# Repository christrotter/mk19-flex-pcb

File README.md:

# mk19-flex-pcb
All credit to: [Cyboard](https://github.com/Cyboard-DigitalTailor/cyboard-public)

Custom flex pcb/cable/thing for the mk19 pcb rev2, an extended version of the Cyboard factory cable.

# ordering notes
## creating gerbers.zip
Follow their docs: 
- https://jlcpcb.com/help/article/495-easyeda-flex-pcb-design-user-guide
- https://jlcpcb.com/help/article/362-how-to-generate-gerber-and-drill-files-in-kicad-7

Ensure you include the User_Drawings layer.

**Example gerber file contents:**
```
mk19-flex-pcb-B_Cu.gbl
mk19-flex-pcb-B_Mask.gbs
mk19-flex-pcb-B_Paste.gbp
mk19-flex-pcb-B_Silkscreen.gbo
mk19-flex-pcb-Edge_Cuts.gm1
mk19-flex-pcb-F_Cu.gtl
mk19-flex-pcb-F_Mask.gts
mk19-flex-pcb-F_Paste.gtp
mk19-flex-pcb-F_Silkscreen.gto
mk19-flex-pcb-NPTH-drl_map.gbr
mk19-flex-pcb-NPTH.drl
mk19-flex-pcb-PTH-drl_map.gbr
mk19-flex-pcb-PTH.drl
mk19-flex-pcb-User_Drawings.gbr
mk19-flex-pcb-gerbers.zip
mk19-flex-pcb-job.gbrjob
```

## submitting the order
- whatever quantity you want
- 0.12 pcb thickness
- polyimide stiffener; 0.1mm
- 0.2mm gold fingers
- colour: white

1. On the initial order page.  The very first page where you add the gerbers.zip file.
2. Veerrrrrrry bottom: 'add pcb remark'
3. Ensure you add a comment in here that says: 
```
Please see 'mk19-flex-pcb-User_Drawings.gbr' for stiffener locations and remarks - there should be only a small amount of stiffener required. I understand this requires extra charges for the small slots - that's fine.
```

# overview

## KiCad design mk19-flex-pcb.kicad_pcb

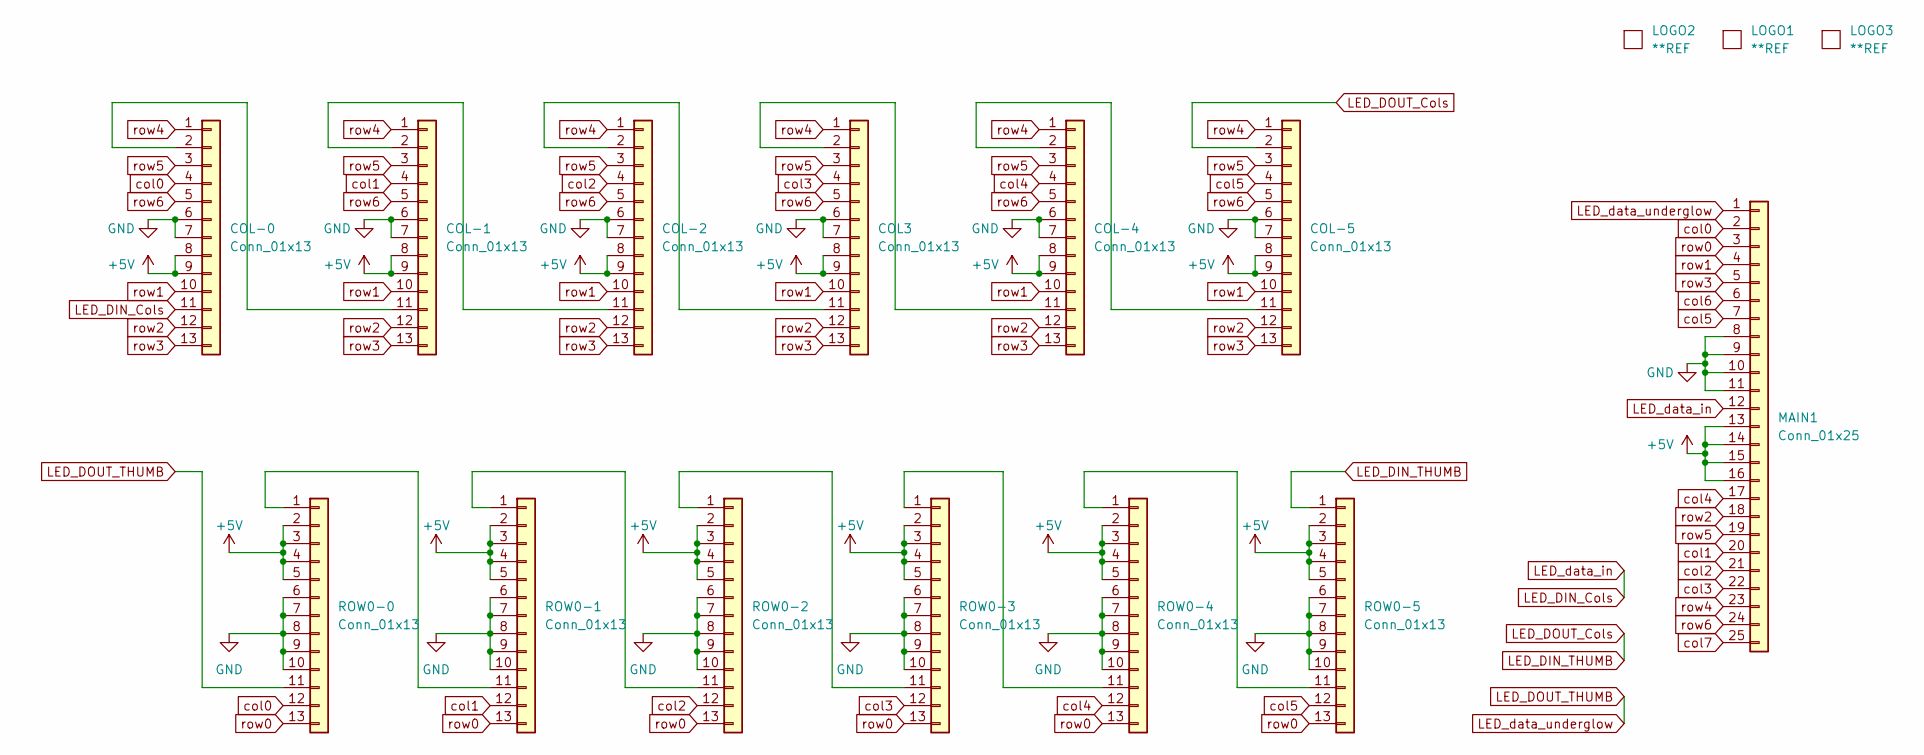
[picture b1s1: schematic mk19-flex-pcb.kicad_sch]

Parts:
COL3: Conn_01x13; FFC Termination 13x0.3 ECT818001568
COL-0, COL-1, COL-2, COL-4, COL-5: Conn_01x13; FFC Termination 13x0.3 ECT818001568
LOGO1: **REF; awesome-logo
LOGO2: **REF; cyboard-logo-10mm
LOGO3: **REF; mk19-flex-pcb-qr-12mm
MAIN1: Conn_01x25; FFC Termination 25x0.3 ECT818001569
ROW0-0, ROW0-1, ROW0-2, ROW0-3, ROW0-4, ROW0-5: Conn_01x13; FFC Termination 13x0.3 ECT818001568

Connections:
+5V: COL3.8, COL3.9, COL-0.8, COL-0.9, COL-1.8, COL-1.9, COL-2.8, COL-2.9, COL-4.8, COL-4.9, COL-5.8, COL-5.9, MAIN1.13, MAIN1.14, MAIN1.15, MAIN1.16, ROW0-0.2, ROW0-0.3, ROW0-0.4, ROW0-0.5, ROW0-1.2, ROW0-1.3, ROW0-1.4, ROW0-1.5, ROW0-2.2, ROW0-2.3, ROW0-2.4, ROW0-2.5, ROW0-3.2, ROW0-3.3, ROW0-3.4, ROW0-3.5, ROW0-4.2, ROW0-4.3, ROW0-4.4, ROW0-4.5, ROW0-5.2, ROW0-5.3, ROW0-5.4, ROW0-5.5
GND: COL3.6, COL3.7, COL-0.6, COL-0.7, COL-1.6, COL-1.7, COL-2.6, COL-2.7, COL-4.6, COL-4.7, COL-5.6, COL-5.7, MAIN1.8, MAIN1.9, MAIN1.10, MAIN1.11, ROW0-0.6, ROW0-0.7, ROW0-0.8, ROW0-0.9, ROW0-0.10, ROW0-1.6, ROW0-1.7, ROW0-1.8, ROW0-1.9, ROW0-1.10, ROW0-2.6, ROW0-2.7, ROW0-2.8, ROW0-2.9, ROW0-2.10, ROW0-3.6, ROW0-3.7, ROW0-3.8, ROW0-3.9, ROW0-3.10, ROW0-4.6, ROW0-4.7, ROW0-4.8, ROW0-4.9, ROW0-4.10, ROW0-5.6, ROW0-5.7, ROW0-5.8, ROW0-5.9, ROW0-5.10
LED_DIN_Cols: COL-0.11, MAIN1.12
LED_DIN_THUMB: COL-5.2, ROW0-5.1
LED_DOUT_THUMB: MAIN1.1, ROW0-0.11
unnamed: COL-0.2, COL-1.11
unnamed: COL-1.2, COL-2.11
unnamed: COL3.11, COL-2.2
unnamed: COL-4.2, COL-5.11
unnamed: COL3.2, COL-4.11
unnamed: ROW0-0.1, ROW0-1.11
unnamed: ROW0-1.1, ROW0-2.11
unnamed: ROW0-2.1, ROW0-3.11
unnamed: ROW0-3.1, ROW0-4.11
unnamed: ROW0-4.1, ROW0-5.11
col0: COL-0.4, MAIN1.2, ROW0-0.12
col1: COL-1.4, MAIN1.20, ROW0-1.12
col2: COL-2.4, MAIN1.21, ROW0-2.12
col3: COL3.4, MAIN1.22, ROW0-3.12
col4: COL-4.4, MAIN1.17, ROW0-4.12
col5: COL-5.4, MAIN1.7, ROW0-5.12
col6: MAIN1.6
col7: MAIN1.25
row0: MAIN1.3, ROW0-0.13, ROW0-1.13, ROW0-2.13, ROW0-3.13, ROW0-4.13, ROW0-5.13
row1: COL3.10, COL-0.10, COL-1.10, COL-2.10, COL-4.10, COL-5.10, MAIN1.4
row2: COL3.12, COL-0.12, COL-1.12, COL-2.12, COL-4.12, COL-5.12, MAIN1.18
row3: COL3.13, COL-0.13, COL-1.13, COL-2.13, COL-4.13, COL-5.13, MAIN1.5
row4: COL3.1, COL-0.1, COL-1.1, COL-2.1, COL-4.1, COL-5.1, MAIN1.23
row5: COL3.3, COL-0.3, COL-1.3, COL-2.3, COL-4.3, COL-5.3, MAIN1.19
row6: COL3.5, COL-0.5, COL-1.5, COL-2.5, COL-4.5, COL-5.5, MAIN1.24

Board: 2 copper layers, 16 parts (0 on the bottom side), 28 nets.

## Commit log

2024-02-25 working flex shape, needs routing
2024-02-25 ready for review
2024-02-25 moving stiffener labels
2024-02-26 adding teardrops, fixing a few odds and ends
2024-02-26 fixing up the teardrops and spacing out vias for better tolerances
2024-02-26 fixing up the tab edge spacing of traces
2024-02-26 final changes before production
2024-02-26 organizing the schematic
2024-02-28 updating readme and docs
2024-02-28 forgot an image file
2024-02-28 forgot an image
